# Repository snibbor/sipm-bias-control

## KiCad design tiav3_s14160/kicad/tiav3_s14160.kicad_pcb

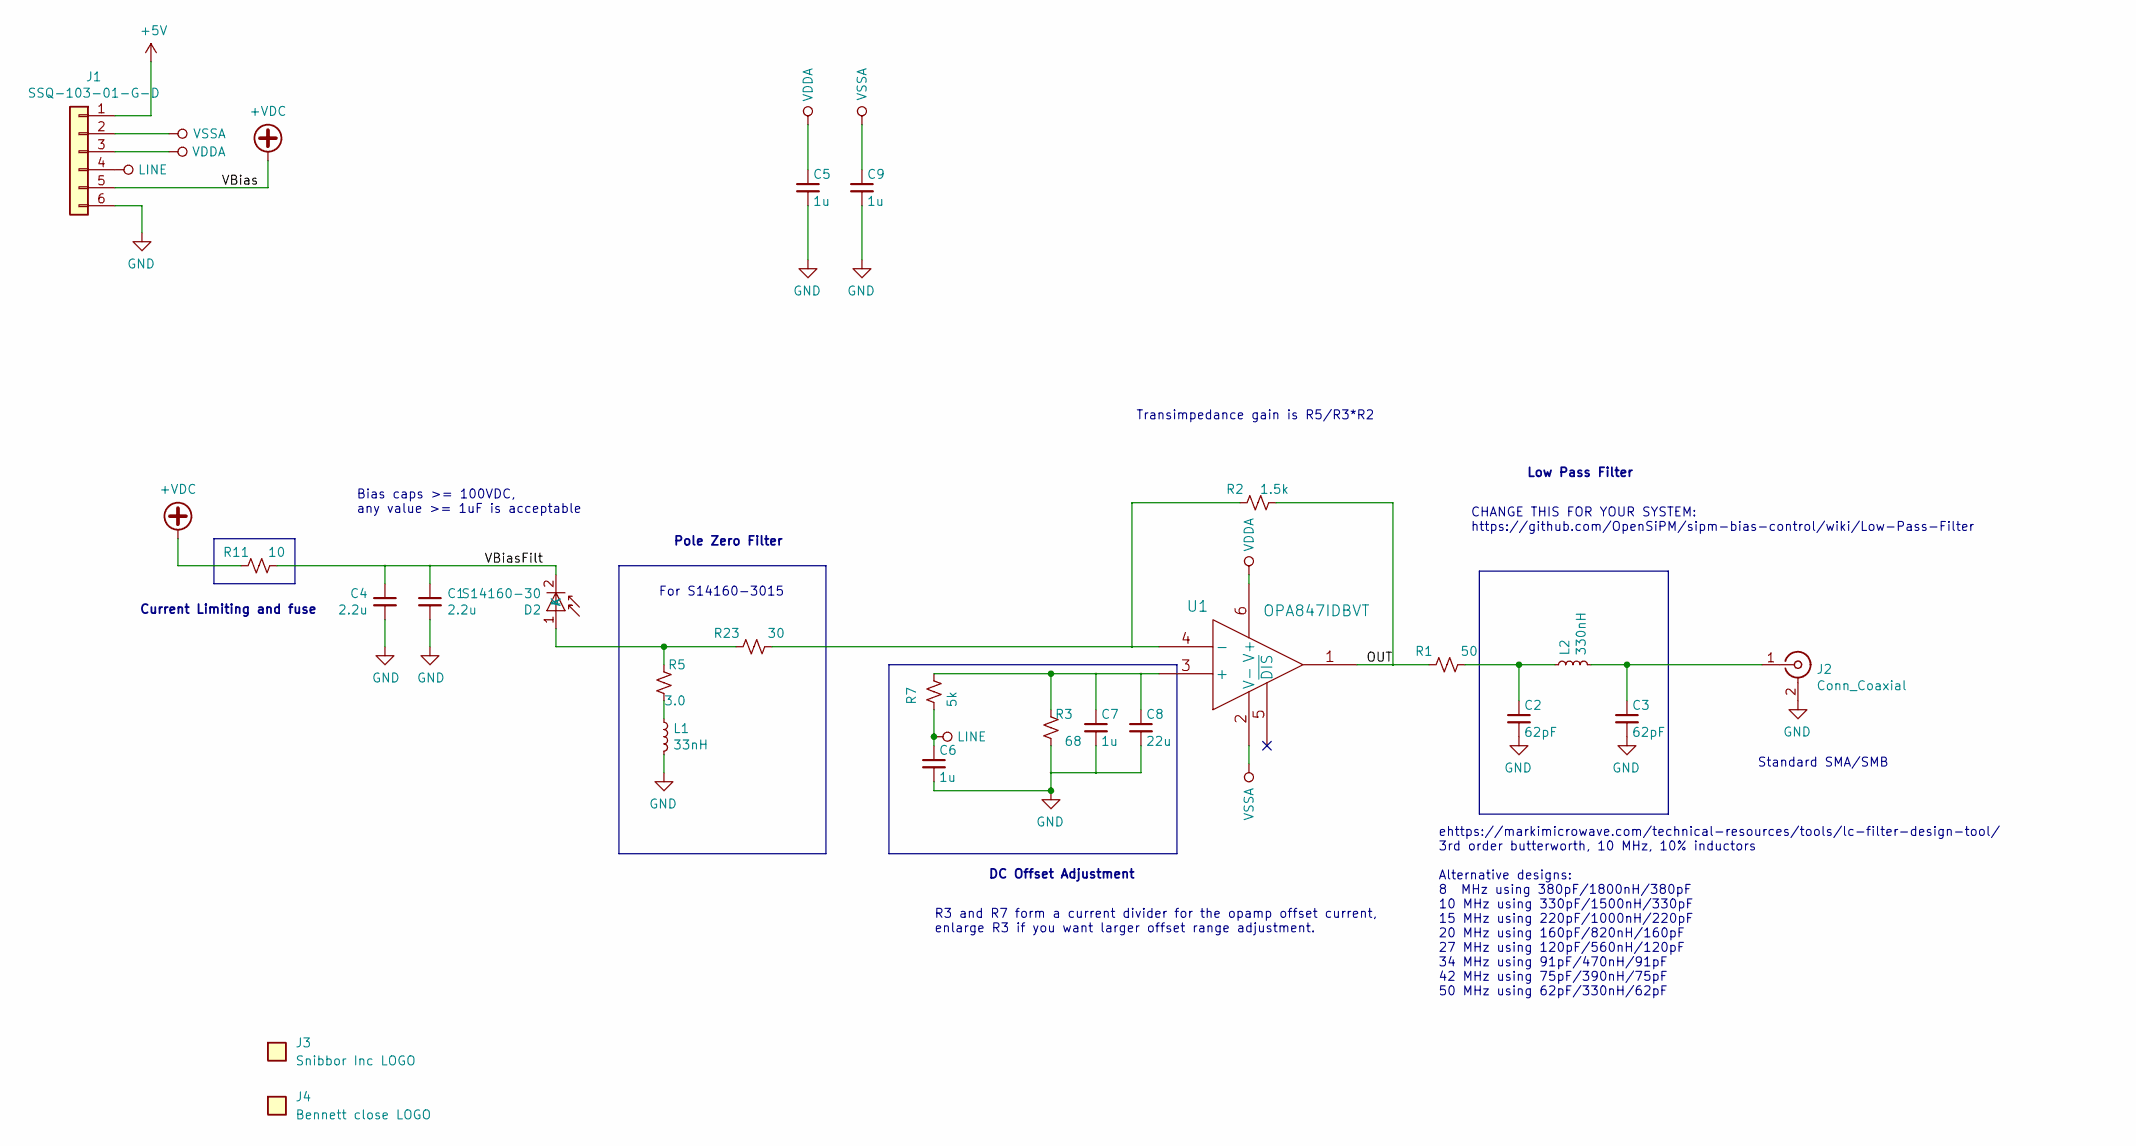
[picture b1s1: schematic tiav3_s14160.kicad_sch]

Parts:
C1, C4: 2.2u; C_1206_3216Metric; Voltage 100V
C2, C3: 62pF; C_0402_1005Metric
C5, C6, C7, C9: 1u; C_0402_1005Metric; Voltage 10V
C8: 22u; C_0603_1608Metric; Voltage 10V
D2: S14160-30
J1: SSQ-103-01-G-D; PinHeader_2x03_P2.54mm_Vertical
J2: Conn_Coaxial; SMB_Jack_Vertical; Digikey WM5528-ND
J3: Snibbor Inc LOGO; snibbor_inc_logo
J4: Bennett close LOGO; Bennett logo close 1 layered
L1: 33nH; L_0603_1608Metric_Pad1.05x0.95mm_HandSolder
L2: 330nH; L_0603_1608Metric; part MLF1005GR56JTD25
R1: 50; R_0402_1005Metric
R2: 1.5k; R_0402_1005Metric
R3: 68; R_0402_1005Metric
R5: 3.0; R_0402_1005Metric
R7: 5k; R_0402_1005Metric
R11: 10; R_0402_1005Metric_Pad0.72x0.64mm_HandSolder
R23: 30; R_0402_1005Metric
U1: OPA847IDBVT

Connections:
+5V: J1.1
+VDC: J1.5, R11.1
/OUT: R1.1, R2.2, U1.1
/VBiasFilt: C1.1, C4.1, D2.2 (K), R11.2
GND: C1.2, C2.2, C3.2, C4.2, C5.2, C6.2, C7.2, C8.2, C9.2, J1.6, J2.2 (Ext), L1.2, R3.1
LINE: C6.1, J1.4, R7.2
unnamed: C2.1, L2.1, R1.2
unnamed: D2.1 (A), R5.2, R23.1
unnamed: C3.1, J2.1 (In), L2.2
unnamed: L1.1, R5.1
unnamed: C7.1, C8.1, R3.2, R7.1, U1.3 (+)
unnamed: R2.1, R23.2, U1.4 (-)
VDDA: C5.1, J1.3, U1.6 (V+)
VSSA: C9.1, J1.2, U1.2 (V-)

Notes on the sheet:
Bias caps >= 100VDC, any value >= 1uF is acceptable
ehttps://markimicrowave.com/technical-resources/tools/lc-filter-design-tool/ 3rd order butterworth, 10 MHz, 10% inductors Alternative designs: 8 MHz using 380pF/1800nH/380pF 10 MHz using 330pF/1500nH/330pF 15 MHz using 220pF/1000nH/220pF 20 MHz using 160pF/820nH/160pF 27 MHz using 120pF/560nH/120pF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
Pole Zero Filter
CHANGE THIS FOR YOUR SYSTEM: https://github.com/OpenSiPM/sipm-bias-control/wiki/Low-Pass-Filter
Low Pass Filter
DC Offset Adjustment
Current Limiting and fuse
R3 and R7 form a current divider for the opamp offset current, enlarge R3 if you want larger offset range adjustment.
Standard SMA/SMB
Transimpedance gain is R5/R3*R2
For S14160-3015

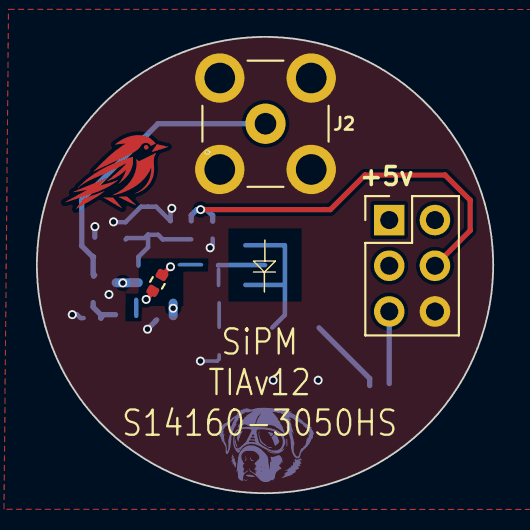
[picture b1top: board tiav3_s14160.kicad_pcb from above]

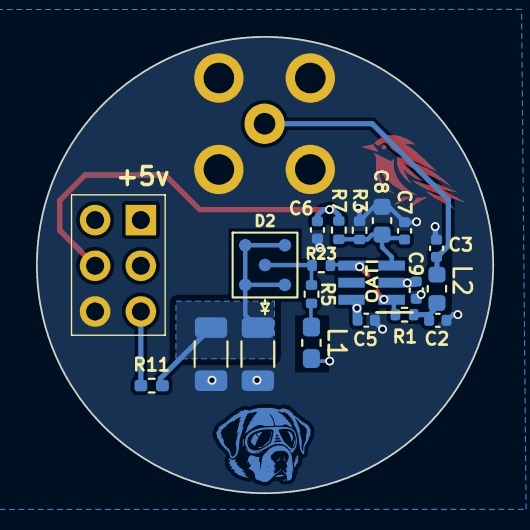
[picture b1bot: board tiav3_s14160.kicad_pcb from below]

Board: 4 copper layers, 25.3 x 25.3 mm, 24 parts (20 on the bottom side), 13 nets.

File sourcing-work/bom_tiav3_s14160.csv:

Board,Refs,Qty,Value,Footprint
tiav3_s14160,C1 C4,2,2.2u,C_1206_3216Metric
tiav3_s14160,C2 C3,2,62pF,C_0402_1005Metric
tiav3_s14160,C5 C6 C7 C9,4,1u,C_0402_1005Metric
tiav3_s14160,C8,1,22u,C_0603_1608Metric
tiav3_s14160,D2,1,S14160-30,S14160-30
tiav3_s14160,J1,1,SSQ-103-01-G-D,PinHeader_2x03_P2.54mm_Vertical
tiav3_s14160,J2,1,Conn_Coaxial,SMB_Jack_Vertical
tiav3_s14160,L1,1,33nH,L_0603_1608Metric_Pad1.05x0.95mm_HandSolder
tiav3_s14160,L2,1,330nH,L_0603_1608Metric
tiav3_s14160,R1,1,50,R_0402_1005Metric
tiav3_s14160,R2,1,1.5k,R_0402_1005Metric
tiav3_s14160,R3,1,68,R_0402_1005Metric
tiav3_s14160,R5,1,3.0,R_0402_1005Metric
tiav3_s14160,R7,1,5k,R_0402_1005Metric
tiav3_s14160,R11,1,10,R_0402_1005Metric_Pad0.72x0.64mm_HandSolder
tiav3_s14160,R23,1,30,R_0402_1005Metric
tiav3_s14160,U1,1,OPA847IDBVT,OPA847IDBVT

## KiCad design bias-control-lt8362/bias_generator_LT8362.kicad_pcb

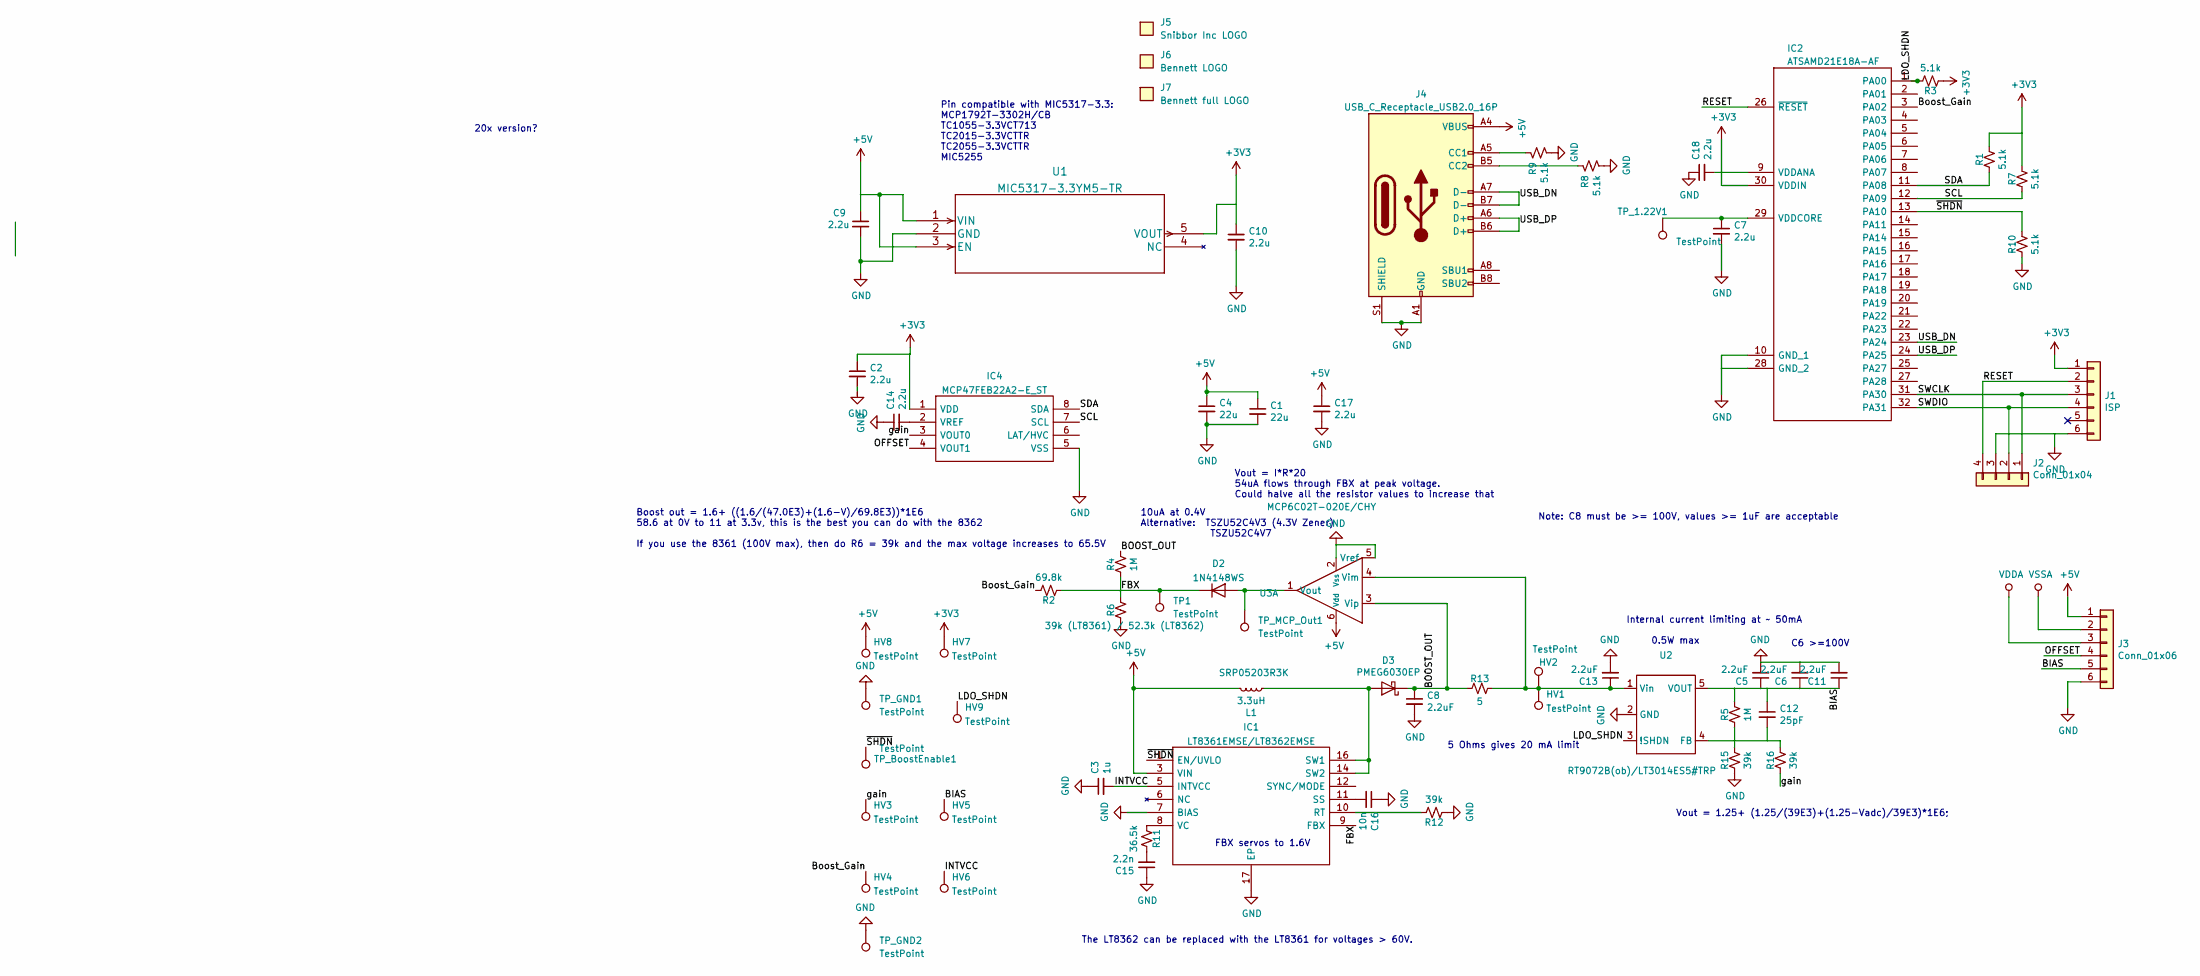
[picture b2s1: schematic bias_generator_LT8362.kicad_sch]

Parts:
C1, C4: 22u; C_0603_1608Metric; Voltage 10V
C2, C7, C9, C10, C14, C17, C18: 2.2u; C_0603_1608Metric
C3: 1u; C_0603_1608Metric
C5, C6, C8, C11, C13: 2.2uF; C_1206_3216Metric; Voltage 100V
C12: 25pF; C_0603_1608Metric
C15: 2.2n; C_0603_1608Metric
C16: 10n; C_0603_1608Metric
D2: 1N4148WS; D_SOD-323F
D3: PMEG6030EP; D_SOD-128
HV1, HV2, HV3, HV4, HV5, HV6, HV7, HV8, HV9: TestPoint; TestPoint_Pad_D1.0mm
IC1: LT8361EMSE/LT8362EMSE; LT8364IMSE-PBF; Mouser Part Number 584-LT8364EMSETRPBF
IC2: ATSAMD21E18A-AF; Manufacturer_Part_Number ATSAMD21E18A-AFT
IC4: MCP47FEB22A2-E_ST; SOP65P640X120-8N; Mouser Part Number 579-MCP47FEB22A2EST
J1: ISP; POGO_ISP
J2: Conn_01x04; PinHeader_1x04_P2.54mm_Vertical_SMD_Pin1Right
J3: Conn_01x06; PinHeader_2x03_P2.54mm_Vertical
J4: USB_C_Receptacle_USB2.0_16P; CUI_UJ20-C-V-C-2-SMT-TR_fixedV2
J5: Snibbor Inc LOGO; snibbor_inc_logo
J6: Bennett LOGO; Bennett logo close 1 layered
J7: Bennett full LOGO; Bennett logo full 1 layered
L1: 3.3uH; SRP05204R7K; MPN SRP05203R3K
R1, R3, R7, R8, R9, R10: 5.1k; R_0603_1608Metric
R2: 69.8k; R_0603_1608Metric
R4, R5: 1M; R_0603_1608Metric
R6: 39k (LT8361) / 52.3k (LT8362); R_0603_1608Metric
R11: 36.5k; R_0603_1608Metric
R12, R15, R16: 39k; R_0603_1608Metric
R13: 5; R_0603_1608Metric
TP1: TestPoint; TestPoint_Pad_D1.0mm
TP_1.22V1: TestPoint; TestPoint_Pad_D1.0mm
TP_BoostEnable1: TestPoint; TestPoint_Pad_D1.0mm
TP_GND1, TP_GND2: TestPoint; TestPoint_Pad_D1.0mm
TP_MCP_Out1: TestPoint; TestPoint_Pad_D1.0mm
U1: MIC5317-3.3YM5-TR
U2: RT9072B(ob)/LT3014ES5#TRP; SOT-23-5
U3: MCP6C02T-020E/CHY; SOT-23-6

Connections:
+3V3: C2.1, C10.1, C18.2, HV7.1, IC2.9 (VDDANA), IC2.30 (VDDIN), IC4.1 (VDD), J1.1, R1.1, R3.2, R7.1, U1.5 (VOUT)
+5V: C1.1, C4.1, C9.1, C17.1, HV8.1, IC1.3 (VIN), J3.1, J4.A4 (VBUS), J4.A9 (VBUS), J4.B4 (VBUS), J4.B9 (VBUS), L1.2, U1.1 (VIN), U1.3 (EN), U3.6 (Vdd)
/BIAS: C5.1, C6.1, C11.1, C12.1, HV5.1, J3.5, R5.1, U2.5 (VOUT)
/BOOST_OUT: C8.1, D3.1 (K), R4.1, R13.2, U3.3 (Vip)
/Boost_Gain: HV4.1, IC2.3 (PA02), R2.1
/FBX: D2.1 (K), IC1.9 (FBX), R2.2, R4.2, R6.1, TP1.1
/INTVCC: C3.2, HV6.1, IC1.5 (INTVCC)
/LDO_SHDN: HV9.1, IC2.1 (PA00), R3.1, U2.3 (!SHDN)
/OFFSET: IC4.4 (VOUT1), J3.4
/RESET: IC2.26 (~RESET), J1.2, J2.4
/SCL: IC2.12 (PA09), IC4.7 (SCL), R7.2
/SDA: IC2.11 (PA08), IC4.8 (SDA), R1.2
/SWCLK: IC2.31 (PA30), J1.3, J2.1
/SWDIO: IC2.32 (PA31), J1.4, J2.2
/USB_DN: IC2.23 (PA24), J4.A7 (D-), J4.B7 (D-)
/USB_DP: IC2.24 (PA25), J4.A6 (D+), J4.B6 (D+)
/gain: HV3.1, IC4.3 (VOUT0), R16.2
/~SHDN: IC1.1 (EN/UVLO), IC2.13 (PA10), R10.1, TP_BoostEnable1.1
GND: C1.2, C2.2, C3.1, C4.2, C5.2, C6.2, C7.2, C8.2, C9.2, C10.2, C11.2, C13.2, C14.1, C15.1, C16.1, C17.2, C18.1, IC1.7 (BIAS), IC1.17 (EP), IC2.10 (GND_1), IC2.28 (GND_2), IC4.5 (VSS), J1.6, J2.3, J3.6, J4.A1 (GND), J4.A12 (GND), J4.B1 (GND), J4.B12 (GND), J4.S1 (SHIELD), R6.2, R8.2, R9.2, R10.2, R12.2, R15.2, TP_GND1.1, TP_GND2.1, U1.2 (GND), U2.2 (GND), U3.2 (Vss), U3.5 (Vref)
unnamed: C15.2, R11.1
unnamed: D2.2 (A), TP_MCP_Out1.1, U3.1 (Vout)
unnamed: D3.2 (A), IC1.14 (SW2), IC1.16 (SW1), L1.1
unnamed: IC1.10 (RT), R12.1
unnamed: C16.2, IC1.11 (SS)
unnamed: IC1.8 (VC), R11.2
unnamed: C7.1, IC2.29 (VDDCORE), TP_1.22V1.1
unnamed: C14.2, IC4.2 (VREF)
unnamed: J4.A5 (CC1), R9.1
unnamed: J4.B5 (CC2), R8.1
unnamed: C12.2, R5.2, R15.1, R16.1, U2.4 (FB)
unnamed: C13.1, HV1.1, HV2.1, R13.1, U2.1 (Vin), U3.4 (Vim)
VDDA: J3.3
VSSA: J3.2

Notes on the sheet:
Note: C8 must be >= 100V, values >= 1uF are acceptable
Vout = I*R*20 54uA flows through FBX at peak voltage. Could halve all the resistor values to increase that
Internal current limiting at ~ 50mA
Pin compatible with MIC5317-3.3: MCP1792T-3302H/CB TC1055-3.3VCT713 TC2015-3.3VCTTR TC2055-3.3VCTTR MIC5255
20x version?
0.5W max
10uA at 0.4V Alternative: TSZU52C4V3 (4.3V Zener) TSZU52C4V7
C6 >=100V
Vout = 1.25+ (1.25/(39E3)+(1.25-Vadc)/39E3)*1E6;
5 Ohms gives 20 mA limit
Boost out = 1.6+ ((1.6/(47.0E3)+(1.6-V)/69.8E3))*1E6 58.6 at 0V to 11 at 3.3v, this is the best you can do with the 8362 If you use the 8361 (100V max), then do R6 = 39k and the max voltage increases to 65.5V
FBX servos to 1.6V
The LT8362 can be replaced with the LT8361 for voltages > 60V.

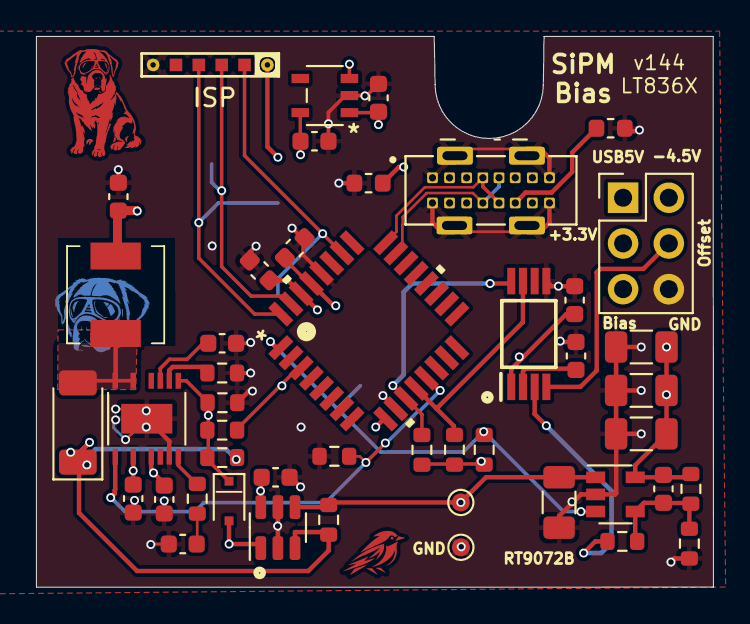
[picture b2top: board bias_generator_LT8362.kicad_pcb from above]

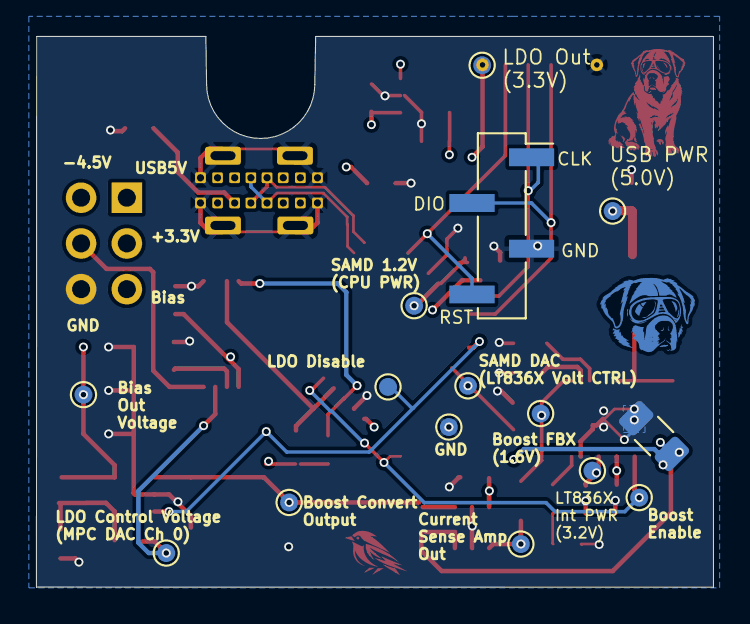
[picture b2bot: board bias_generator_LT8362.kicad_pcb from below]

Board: 4 copper layers, 37.6 x 30.6 mm, 64 parts (16 on the bottom side), 31 nets.

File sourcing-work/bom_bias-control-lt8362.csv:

Board,Refs,Qty,Value,Footprint
bias-control-lt8362,C1 C4,2,22u,C_0603_1608Metric
bias-control-lt8362,C2 C7 C9 C10 C14 C17 C18,7,2.2u,C_0603_1608Metric
bias-control-lt8362,C3,1,1u,C_0603_1608Metric
bias-control-lt8362,C5 C6 C8 C11 C13,5,2.2uF,C_1206_3216Metric
bias-control-lt8362,C12,1,25pF,C_0603_1608Metric
bias-control-lt8362,C15,1,2.2n,C_0603_1608Metric
bias-control-lt8362,C16,1,10n,C_0603_1608Metric
bias-control-lt8362,D2,1,1N4148WS,D_SOD-323F
bias-control-lt8362,D3,1,PMEG6030EP,D_SOD-128
bias-control-lt8362,HV1 HV2 HV3 HV4 HV5 HV6 HV9 TP1 TP_1.22V1 TP_BoostEnable1 TP_GND1 TP_GND2 TP_MCP_Out1,13,TestPoint,TestPoint_Pad_D1.0mm
bias-control-lt8362,IC1,1,LT8361EMSE/LT8362EMSE,LT8364IMSE-PBF
bias-control-lt8362,IC2,1,ATSAMD21E18A-AF,ATSAMD21E18A-AF
bias-control-lt8362,IC4,1,MCP47FEB22A2-E_ST,SOP65P640X120-8N
bias-control-lt8362,J2,1,Conn_01x04,PinHeader_1x04_P2.54mm_Vertical_SMD_Pin1Right
bias-control-lt8362,J3,1,Conn_01x06,PinHeader_2x03_P2.54mm_Vertical
bias-control-lt8362,J4,1,USB_C_Receptacle_USB2.0_16P,CUI_UJ20-C-V-C-2-SMT-TR_fixedV2
bias-control-lt8362,L1,1,3.3uH,SRP05204R7K
bias-control-lt8362,R1 R3 R7 R8 R9 R10,6,5.1k,R_0603_1608Metric
bias-control-lt8362,R2,1,69.8k,R_0603_1608Metric
bias-control-lt8362,R4 R5,2,1M,R_0603_1608Metric
bias-control-lt8362,R6,1,39k (LT8361) / 52.3k (LT8362),R_0603_1608Metric
bias-control-lt8362,R11,1,36.5k,R_0603_1608Metric
bias-control-lt8362,R12 R15 R16,3,39k,R_0603_1608Metric
bias-control-lt8362,R13,1,5,R_0603_1608Metric
bias-control-lt8362,U1,1,MIC5317-3.3YM5-TR,MIC5317-3.3YM5-TR
bias-control-lt8362,U2,1,RT9072B,SOT-23-5
bias-control-lt8362,U3,1,MCP6C02T-020E/CHY,SOT-23-6

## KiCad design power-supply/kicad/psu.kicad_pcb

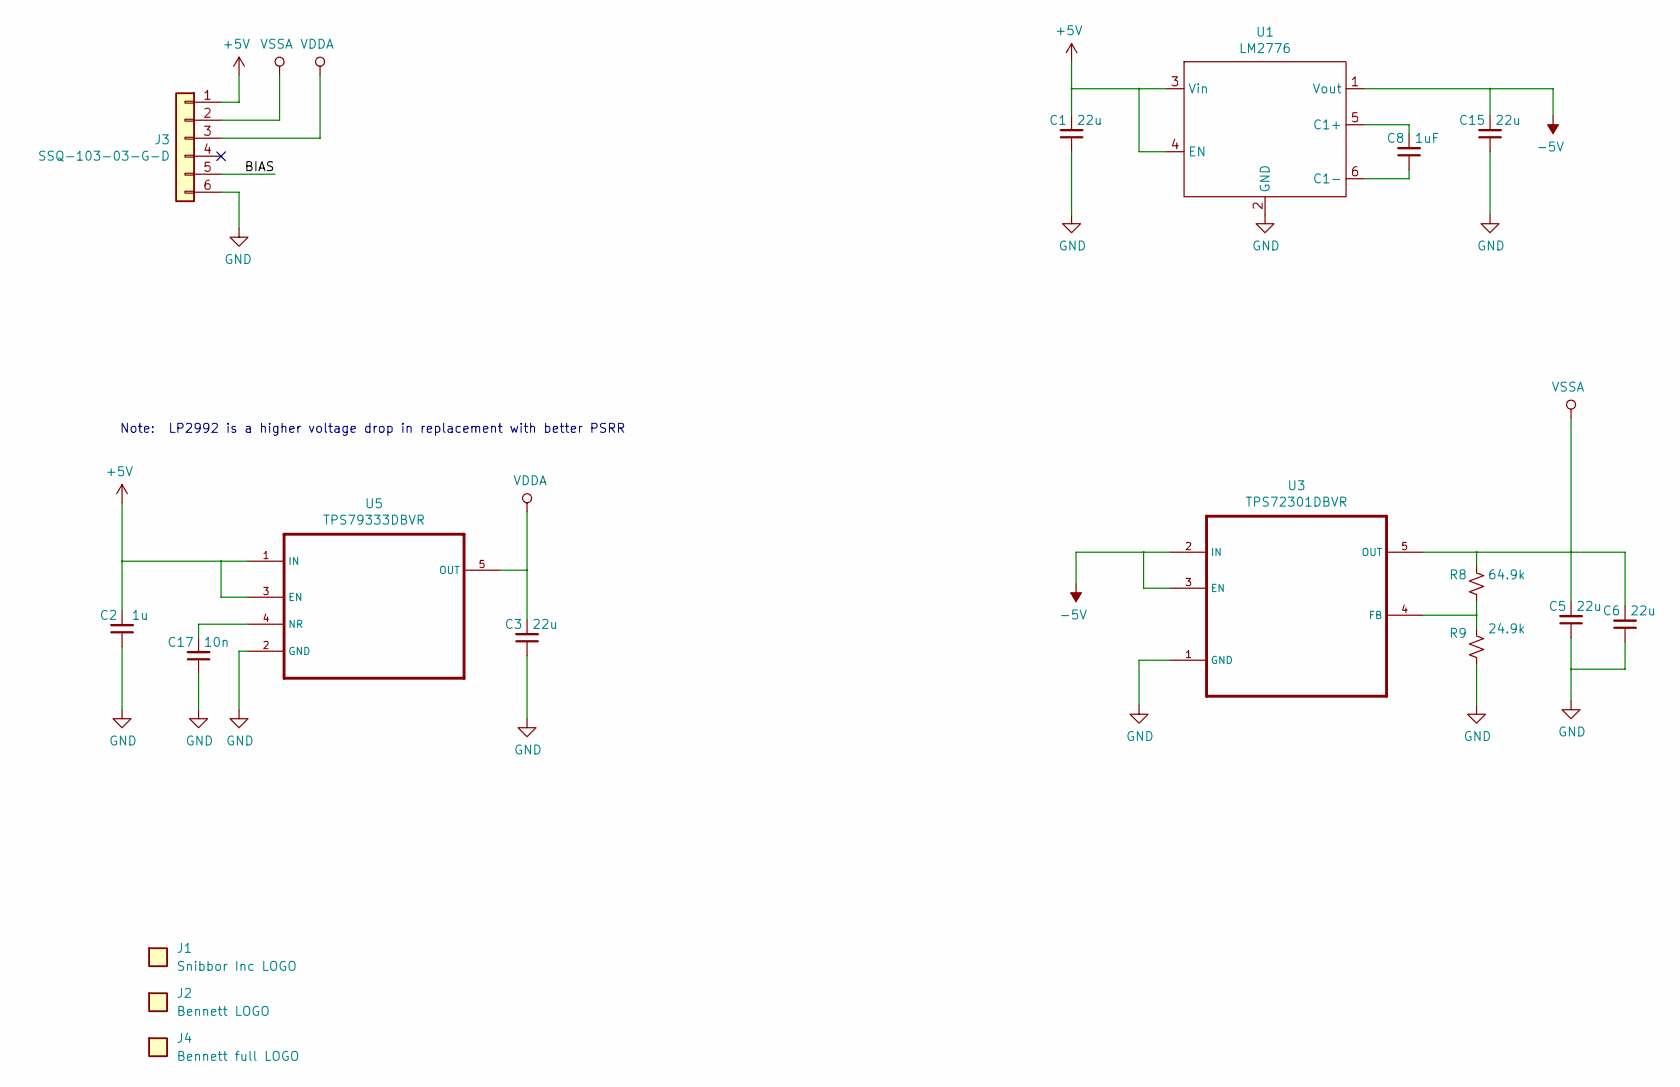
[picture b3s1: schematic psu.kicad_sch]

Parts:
C1, C3, C5, C6, C15: 22u; C_0603_1608Metric
C2: 1u; C_0603_1608Metric
C8: 1uF; C_0603_1608Metric
C17: 10n; C_0603_1608Metric
J1: Snibbor Inc LOGO; snibbor_inc_logo
J2: Bennett LOGO; Bennett logo close 1 layered
J3: SSQ-103-03-G-D; PinHeader_2x03_P2.54mm_Vertical
J4: Bennett full LOGO; Bennett logo full 1 layered
R8: 64.9k; R_0603_1608Metric
R9: 24.9k; R_0603_1608Metric
U1: LM2776; LM2776DBVR
U3: TPS72301DBVR
U5: TPS79333DBVR

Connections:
+5V: C1.2, C2.2, J3.1, U1.3 (Vin), U1.4 (EN), U5.1 (IN), U5.3 (EN)
-5V: C15.2, U1.1 (Vout), U3.2 (IN), U3.3 (EN)
/BIAS: J3.5
GND: C1.1, C2.1, C3.1, C5.1, C6.1, C15.1, C17.1, J3.6, R9.1, U1.2 (GND), U3.1 (GND), U5.2 (GND)
unnamed: C8.2, U1.5 (C1+)
unnamed: C8.1, U1.6 (C1-)
unnamed: R8.1, R9.2, U3.4 (FB)
unnamed: C17.2, U5.4 (NR)
VDDA: C3.2, J3.3, U5.5 (OUT)
VSSA: C5.2, C6.2, J3.2, R8.2, U3.5 (OUT)

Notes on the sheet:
Note: LP2992 is a higher voltage drop in replacement with better PSRR

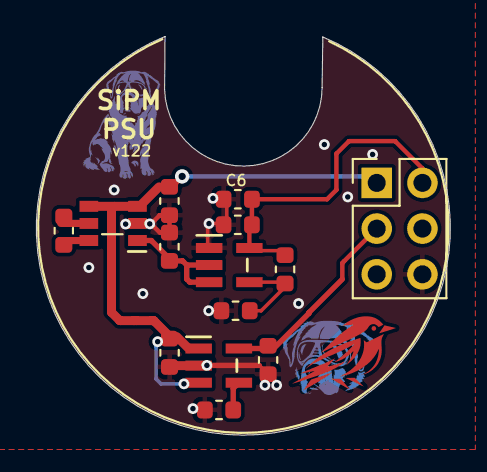
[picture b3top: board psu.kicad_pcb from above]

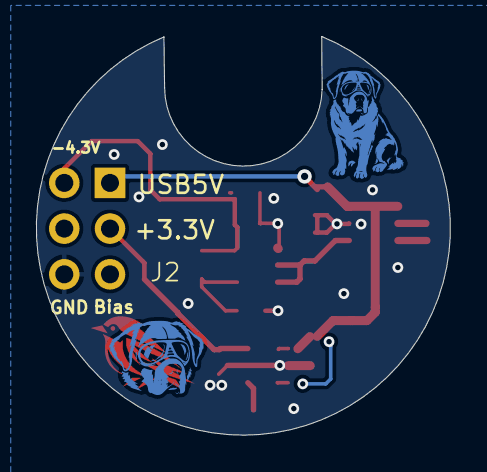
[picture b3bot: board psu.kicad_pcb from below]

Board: 2 copper layers, 23.0 x 22.1 mm, 17 parts (2 on the bottom side), 9 nets.

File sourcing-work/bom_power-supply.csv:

Board,Refs,Qty,Value,Footprint
power-supply,C1 C3 C5 C6 C15,5,22u,C_0603_1608Metric
power-supply,C2 C8,2,1u,C_0603_1608Metric
power-supply,C17,1,10n,C_0603_1608Metric
power-supply,J3,1,SSQ-103-03-G-D,PinHeader_2x03_P2.54mm_Vertical
power-supply,R8,1,64.9k,R_0603_1608Metric
power-supply,R9,1,24.9k,R_0603_1608Metric
power-supply,U1,1,LM2776,LM2776DBVR
power-supply,U3,1,TPS72301DBVR,TPS72301DBVR
power-supply,U5,1,TPS79333DBVR,TPS79333DBVR

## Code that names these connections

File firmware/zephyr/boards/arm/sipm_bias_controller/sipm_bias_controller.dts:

/*
 * SPDX-License-Identifier: Apache-2.0
 * SiPM Bias Controller board (ATSAMD21E18A-AF).
 *
 * Pinout (verified against bias_generator_LT8362.kicad_sch):
 *   PA00 = LDO_SHDN (HV LDO shutdown, active-high disables)
 *   PA02 = Boost_Gain (DAC0 -> LT836X feedback)
 *   PA08 = SDA (SERCOM0 PAD0, to MCP47FEB22)
 *   PA09 = SCL (SERCOM0 PAD1, to MCP47FEB22)
 *   PA10 = ~SHDN (LT836X boost shutdown, active-low disables)
 *   PA24/PA25 = USB DM/DP
 */

/dts-v1/;
#include <atmel/samd21.dtsi>
#include <atmel/samx2xx18.dtsi>
#include "sipm_bias_controller-pinctrl.dtsi"

/ {
	model = "sipm_bias_controller";
	compatible = "applikate,sipm_bias_controller",
		     "atmel,samd21e18a", "atmel,samd21";

	chosen {
		zephyr,console = &cdc_acm_uart0;
		zephyr,shell-uart = &cdc_acm_uart0;
		zephyr,sram = &sram0;
		zephyr,flash = &flash0;
		zephyr,code-partition = &slot0_partition;
		zephyr,boot-mode = &boot_mode0;
	};

	/* Retained memory for boot mode flag (warm-reset persistent). */
	sram_retainedmem: sram@20007ff0 {
		compatible = "zephyr,memory-region", "mmio-sram";
		reg = <0x20007FF0 0x10>;
		zephyr,memory-region = "RetainedMem";
		status = "okay";

		retainedmem {
			compatible = "zephyr,retained-ram";
			status = "okay";
			#address-cells = <1>;
			#size-cells = <1>;

			boot_mode0: boot_mode@0 {
				compatible = "zephyr,retention";
				status = "okay";
				reg = <0x0 0x4>;
				prefix = [08 04];
				checksum = <1>;
			};
		};
	};

	/* High-voltage LDO shutdown line. Net: LDO_SHDN.
	 * Active-high *signal* disables the LDO; flag as ACTIVE_HIGH so
	 * gpio_pin_set_dt(.., 1) means "shut down".
	 */
	hv_ldo: hv_ldo {
		compatible = "gpio-leds";
		hv_ldo_shdn: hv_ldo_shdn {
			gpios = <&porta 0 GPIO_ACTIVE_HIGH>;
			label = "HV_LDO_SHDN";
		};
	};

	/* LT836X boost converter shutdown line. Net: ~SHDN.
	 * Active-low signal: drive HIGH to run, LOW to shut down.
	 * Flagged as ACTIVE_LOW so gpio_pin_set_dt(.., 1) means "enable boost".
	 */
	boost_en: boost_en {
		compatible = "gpio-leds";
		boost_shdn: boost_shdn {
			gpios = <&porta 10 GPIO_ACTIVE_LOW>;
			label = "BOOST_SHDN";
		};
	};
};

zephyr_udc0: &usb0 {
	status = "okay";
	pinctrl-0 = <&usb_dc_default>;
	pinctrl-names = "default";
};

&zephyr_udc0 {
	cdc_acm_uart0: cdc_acm_uart0 {
		compatible = "zephyr,cdc-acm-uart";
	};
};

&cpu0 {
	clock-frequency = <48000000>;
};

/* I2C0 on SERCOM0 (PA08 SDA, PA09 SCL) -> MCP47FEB22 DAC */
&sercom0 {
	status = "okay";
	compatible = "atmel,sam0-i2c";
	clock-frequency = <I2C_BITRATE_STANDARD>;
	#address-cells = <1>;
	#size-cells = <0>;
	pinctrl-0 = <&sercom0_i2c_default>;
	pinctrl-names = "default";

	/* MCP47FEB22 7-bit address. The Arduino code uses i2c_address=2
	 * which on the MCP47FEB22 selects the A2 variant -> 0x62.
	 * Verify against the actual part marking; common addresses are
	 * 0x60 (A0), 0x61 (A1), 0x62 (A2), 0x63 (A3).
	 */
	mcp47feb22: mcp47feb22@62 {
		compatible = "microchip,mcp47feb22";
		reg = <0x62>;
		status = "okay";
		label = "BIAS_DAC";
	};
};

/* On-chip DAC: drives Boost_Gain on PA02 (LT836X feedback). */
&dac0 {
	status = "okay";
};

/* Shrink main SRAM to exclude retained memory region */
&sram0 {
	reg = <0x20000000 0x7FF0>;
};

&flash0 {
	erase-block-size = <256>;

	partitions {
		compatible = "fixed-partitions";
		#address-cells = <1>;
		#size-cells = <1>;

		/* MCUboot bootloader: 48 KiB at 0x00000 */
		boot_partition: partition@0 {
			label = "mcuboot";
			reg = <0x00000000 DT_SIZE_K(48)>;
			read-only;
		};

		/* Application image (slot 0): 100 KiB at 0x0C000 */
		slot0_partition: partition@c000 {
			label = "image-0";
			reg = <0x0000C000 DT_SIZE_K(100)>;
		};

		/* DFU staging image (slot 1): 100 KiB at 0x25000 */
		slot1_partition: partition@25000 {
			label = "image-1";
			reg = <0x00025000 DT_SIZE_K(100)>;
		};

		/* NVS for calibration (offset, g42, g50): 8 KiB at 0x3E000 */
		storage_partition: partition@3e000 {
			label = "storage";
			reg = <0x0003E000 DT_SIZE_K(8)>;
		};
	};
};

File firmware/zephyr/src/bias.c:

/*
 * SPDX-License-Identifier: Apache-2.0
 *
 * SiPM bias control core. Translates between user-facing units
 * (millivolts) and the underlying DAC DNs, drives the MCP47FEB22 for
 * gain/offset, drives the on-chip DAC on PA02 for the LT836X feedback,
 * and manages the boost/LDO enable lines.
 *
 * Voltage model is identical to the Arduino sketch
 * (firmware/LT836X/bias_with_offset_LT836X/bias_with_offset_LT836X.ino):
 *
 *   LT8361:  Vout(mV) = 1600 + ((1600/39000 + 1600/69800)
 *                              - dn*(3300/1024)/69800) * 1e6
 *   LT8362:  Vout(mV) = 1600 + ((1600/52300 + 1600/69800)
 *                              - dn*(3300/1024)/69800) * 1e6
 */

#include <zephyr/device.h>
#include <zephyr/devicetree.h>
#include <zephyr/drivers/dac.h>
#include <zephyr/drivers/gpio.h>
#include <zephyr/logging/log.h>
#include <zephyr/settings/settings.h>
#include <stdlib.h>
#include "bias.h"
#include "mcp47feb22.h"

LOG_MODULE_REGISTER(bias, LOG_LEVEL_INF);

#define BOOST_DAC_CHANNEL 0
#define BOOST_DAC_RESOLUTION 10  /* 10-bit, matches analogWriteResolution(10) */

static const struct device *boost_dac = DEVICE_DT_GET(DT_NODELABEL(dac0));
static const struct gpio_dt_spec hv_ldo_shdn =
	GPIO_DT_SPEC_GET(DT_NODELABEL(hv_ldo_shdn), gpios);
static const struct gpio_dt_spec boost_shdn =
	GPIO_DT_SPEC_GET(DT_NODELABEL(boost_shdn), gpios);

/* Defaults match the Arduino sketch's per-variant block. */
#if defined(CONFIG_BIAS_LT8361)
static uint16_t s_gain   = 3500;
static uint16_t s_g42    = 2538;
static uint16_t s_g50    = 3063;
static uint16_t s_offset = 220;
static uint16_t s_boost_dn = 130;  /* ~59.8 V on LT8361 */
#define BIAS_FB_R 39000
#define BIAS_OFFSET_INTERCEPT_UV 65548000
#elif defined(CONFIG_BIAS_LT8362)
static uint16_t s_gain   = 3500;
static uint16_t s_g42    = 3215;
static uint16_t s_g50    = 3870;
static uint16_t s_offset = 220;
static uint16_t s_boost_dn = 67;   /* ~52.3 V on LT8362 */
#define BIAS_FB_R 52300
#define BIAS_OFFSET_INTERCEPT_UV 55120000
#else
#error "Select a boost converter variant: CONFIG_BIAS_LT8361 or CONFIG_BIAS_LT8362"
#endif

static bool s_on = false;

/* --- voltage <-> DN helpers (linear interp on the gain DAC) --- */

uint32_t bias_gain_to_mv(uint16_t gain)
{
	return (((int32_t)gain - s_g42) * 8000
		+ 42000 * ((int32_t)s_g50 - s_g42))
		/ (s_g50 - s_g42);
}

uint16_t bias_mv_to_gain(uint32_t mv)
{
	return (((int32_t)s_g50 - s_g42) * ((int32_t)mv - 42000)
		+ s_g42 * 8000) / 8000;
}

float bias_boost_dn_to_v(uint16_t dn)
{
	float t = (1600.0f / (float)BIAS_FB_R + 1600.0f / 69800.0f)
		  - dn * (3300.0f / 1024.0f) / 69800.0f;
	return (1600.0f + t * 1000000.0f) / 1000.0f;
}

uint16_t bias_v_to_boost_dn(float v)
{
	float dn = (v * 1e6f - (float)BIAS_OFFSET_INTERCEPT_UV) / -46170.0f;
	if (dn < 0)    return 0;
	if (dn > 1023) return 1023;
	return (uint16_t)(dn + 0.5f);
}

/* --- DAC + GPIO --- */

static int push_bias_dac(void)
{
	/* MCP47FEB22 channel mapping matches Arduino sketch:
	 *   mcp.analogWrite(4095 - gain, offset);
	 * i.e. channel 0 carries (4095 - gain); channel 1 carries offset.
	 */
	return mcp47feb22_write((4095 - s_gain) & 0x0FFF, s_offset & 0x0FFF);
}

static int push_boost_dac(void)
{
	struct dac_channel_cfg cfg = {
		.channel_id = BOOST_DAC_CHANNEL,
		.resolution = BOOST_DAC_RESOLUTION,
		.buffered = false,
	};
	int rc = dac_channel_setup(boost_dac, &cfg);
	if (rc) {
		LOG_ERR("DAC setup failed: %d", rc);
		return rc;
	}
	return dac_write_value(boost_dac, BOOST_DAC_CHANNEL, s_boost_dn);
}

int bias_set_on(bool on)
{
	s_on = on;
	gpio_pin_set_dt(&boost_shdn, on ? 1 : 0);   /* active-low at silicon */
	gpio_pin_set_dt(&hv_ldo_shdn, on ? 0 : 1);  /* active-high disables */
	return 0;
}

bool bias_is_on(void) { return s_on; }

int bias_set_gain(uint16_t gain)
{
	if (gain > 4095) return -EINVAL;
	s_gain = gain;
	return push_bias_dac();
}

int bias_set_offset(uint16_t offset)
{
	if (offset > 4095) return -EINVAL;
	s_offset = offset;
	return push_bias_dac();
}

uint16_t bias_get_gain(void)   { return s_gain; }
uint16_t bias_get_offset(void) { return s_offset; }

int bias_set_boost_dn(uint16_t dn)
{
	if (dn > 1023) return -EINVAL;
	s_boost_dn = dn;
	return push_boost_dac();
}

uint16_t bias_get_boost_dn(void) { return s_boost_dn; }

int bias_set_calibration(uint16_t g42, uint16_t g50)
{
	if (g42 == g50) return -EINVAL;
	s_g42 = g42;
	s_g50 = g50;
	return 0;
}

void bias_get_calibration(uint16_t *g42, uint16_t *g50)
{
	if (g42) *g42 = s_g42;
	if (g50) *g50 = s_g50;
}

/* --- NVS persistence via settings subsystem --- */

#define CAL_KEY "bias/cal"

struct cal_blob {
	uint16_t offset;
	uint16_t g42;
	uint16_t g50;
};

static int cal_set_handler(const char *key, size_t len,
			   settings_read_cb read_cb, void *cb_arg)
{
	struct cal_blob blob;

	ARG_UNUSED(key);
	if (len != sizeof(blob)) return -EINVAL;

	int rc = read_cb(cb_arg, &blob, sizeof(blob));
	if (rc < 0) return rc;

	if (blob.offset <= 2000) s_offset = blob.offset;
	if (blob.g42 >= 20 && blob.g42 <= 4000) s_g42 = blob.g42;
	if (blob.g50 >= 20 && blob.g50 <= 4000) s_g50 = blob.g50;
	LOG_INF("Loaded cal: offset=%u g42=%u g50=%u", s_offset, s_g42, s_g50);
	return 0;
}

SETTINGS_STATIC_HANDLER_DEFINE(bias_cal, "bias", NULL, cal_set_handler,
			       NULL, NULL);

int bias_save(void)
{
	struct cal_blob blob = { .offset = s_offset, .g42 = s_g42, .g50 = s_g50 };
	return settings_save_one(CAL_KEY, &blob, sizeof(blob));
}

int bias_load(void)
{
	return settings_load_subtree("bias");
}

/* --- init --- */

int bias_init(void)
{
	int rc;

	if (!gpio_is_ready_dt(&hv_ldo_shdn) || !gpio_is_ready_dt(&boost_shdn)) {
		LOG_ERR("GPIOs not ready");
		return -ENODEV;
	}

	/* Default: shut down both rails until app raises bias_set_on. */
	gpio_pin_configure_dt(&hv_ldo_shdn, GPIO_OUTPUT_ACTIVE);   /* shut */
	gpio_pin_configure_dt(&boost_shdn, GPIO_OUTPUT_INACTIVE);  /* shut */

	if (!device_is_ready(boost_dac)) {
		LOG_ERR("DAC not ready");
		return -ENODEV;
	}

	rc = mcp47feb22_init();
	if (rc) {
		LOG_WRN("MCP47FEB22 init failed: %d (continuing)", rc);
	}

	rc = settings_subsys_init();
	if (rc) {
		LOG_WRN("settings init: %d", rc);
	} else {
		bias_load();
	}

	push_bias_dac();
	push_boost_dac();
	return 0;
}

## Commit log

2026-03-18 Restore deleted firmware
    Currently the #define is set to LT8361. Be sure to change this if you use the LT8362 resistor configuration or your default voltages will be off.
2026-05-25 Tune tiav3 LPF values and export gerbers
    Update LPF component values (560nH->330nH, 120pF->62pF) and tighten via diameter/drill DRC. Redirect plot/step outputs to ../manufacturing/ and commit the generated gerber set.
2026-05-25 fix: change vias to 0.3/0.5mm diameter for tiav3_s14160, export gerbers
2026-05-25 Update bias generator and power supply boards, export gerbers
2026-05-27 Update KiCad designs for all 3 boards and re-export gerbers
    - bias-control-lt8362: schematic + PCB updates, exported gerbers
    including new B_Paste/F_Paste layers
    - power-supply: schematic + PCB updates, re-exported gerbers with new
    naming (.gbl/.gbs/.gto/.gtl/.gts) replacing old .gbr files, added
    paste layer exports
    - tiav3_s14160: schematic + PCB updates, re-exported gerbers with new
2026-05-27 Add DigiKey sourcing workflow for all 3 boards
    Tooling and deliverables for sourcing the BOMs of bias-control-lt8362,
    power-supply, and tiav3_s14160 boards from DigiKey:
    - digikey_bom_manager.csv: upload to https://www.digikey.com/bom to
    load all 47 line items / 160 units (2 boards' worth) into a cart
    - DESIGN_NOTES.md: per-component function explanations and rationale
    for every substitution made vs the original schematic
2026-05-27 Add initial Zephyr RTOS port of the SiPM bias controller firmware
    Ports the Arduino sketch (firmware/LT836X/bias_with_offset_LT836X) to
    Zephyr targeting the ATSAMD21E18A on the bias_generator_LT8362 PCB.
    Application:
    - USB CDC-ACM shell for runtime commands (on/off, gain, offset,
    voltage, millivolts, offset_voltage, boost, ...)
    - MCUboot DFU support via sysbuild for field firmware updates
2026-06-13 sourcing, ordering, and assembling
2026-06-14 updating s14160-3050HS footprint
2026-06-14 fix S14160-3050HS footprint again, regen gerbers

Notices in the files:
parts and their libraries:
Copyright 2021 Accelerated Designs. All rights reserved.
Copyright 2016 Accelerated Designs. All rights reserved.
